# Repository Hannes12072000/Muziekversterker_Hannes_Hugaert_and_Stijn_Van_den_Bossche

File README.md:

# Muziekversterker_Hannes_Hugaert_and_Stijn_Van_den_bossche
 
onderwerp:  Touch muziekversterker
naam:   Hannes Hugaert & Stijn Van den bossche

Korte beschrijving:
Wij gaan een muziekversterker maken die voorzien is van 2 channels en een microfoon. Op deze versterker kunnen we de tonen regelen (treble, medium en bass) maar we kunnen ook het volume regelen. Onze sliders zijn geen gewone mechanische sliders, we voorzien touchpads als sliders. Om feedback over het volume en de tonen te geven, voorzien we ledjes naast de touchpads om het huidige niveau weer te geven.

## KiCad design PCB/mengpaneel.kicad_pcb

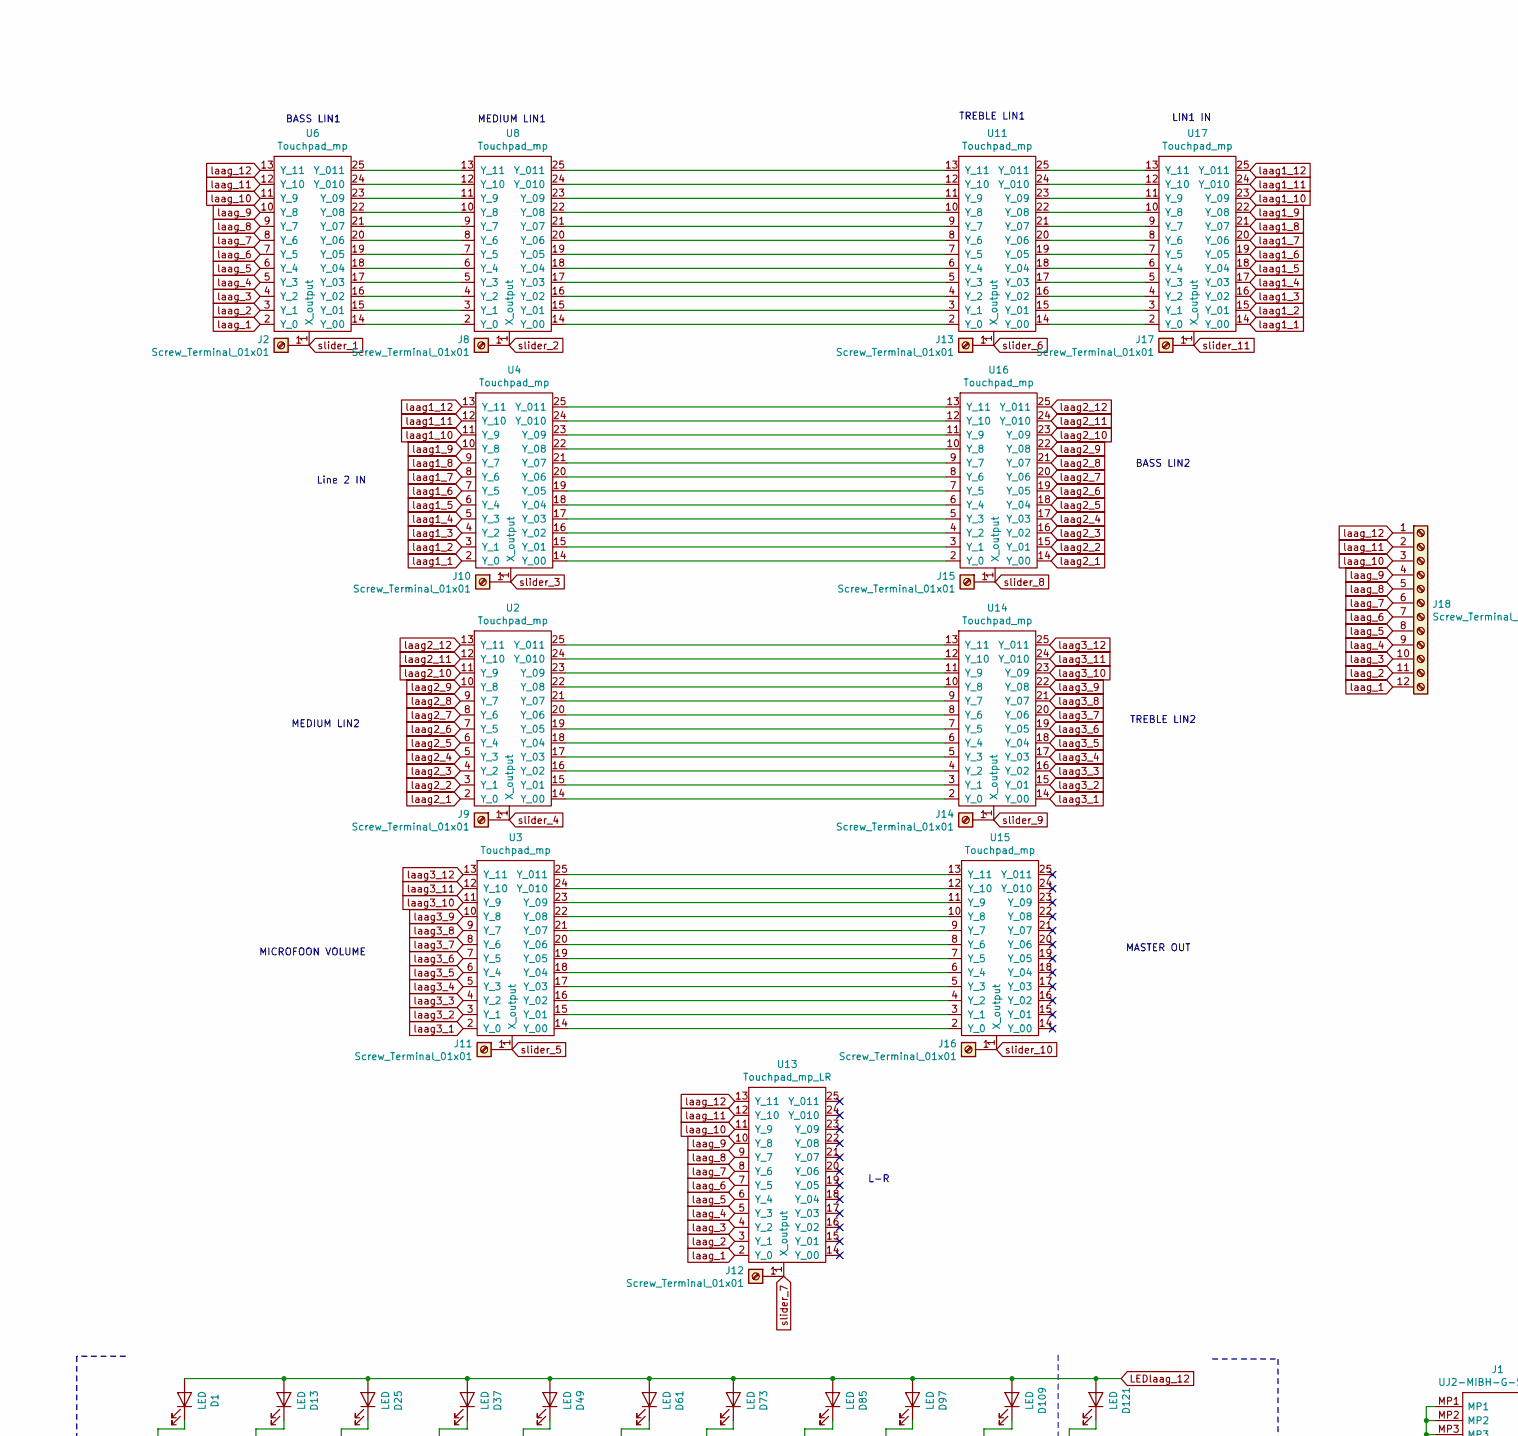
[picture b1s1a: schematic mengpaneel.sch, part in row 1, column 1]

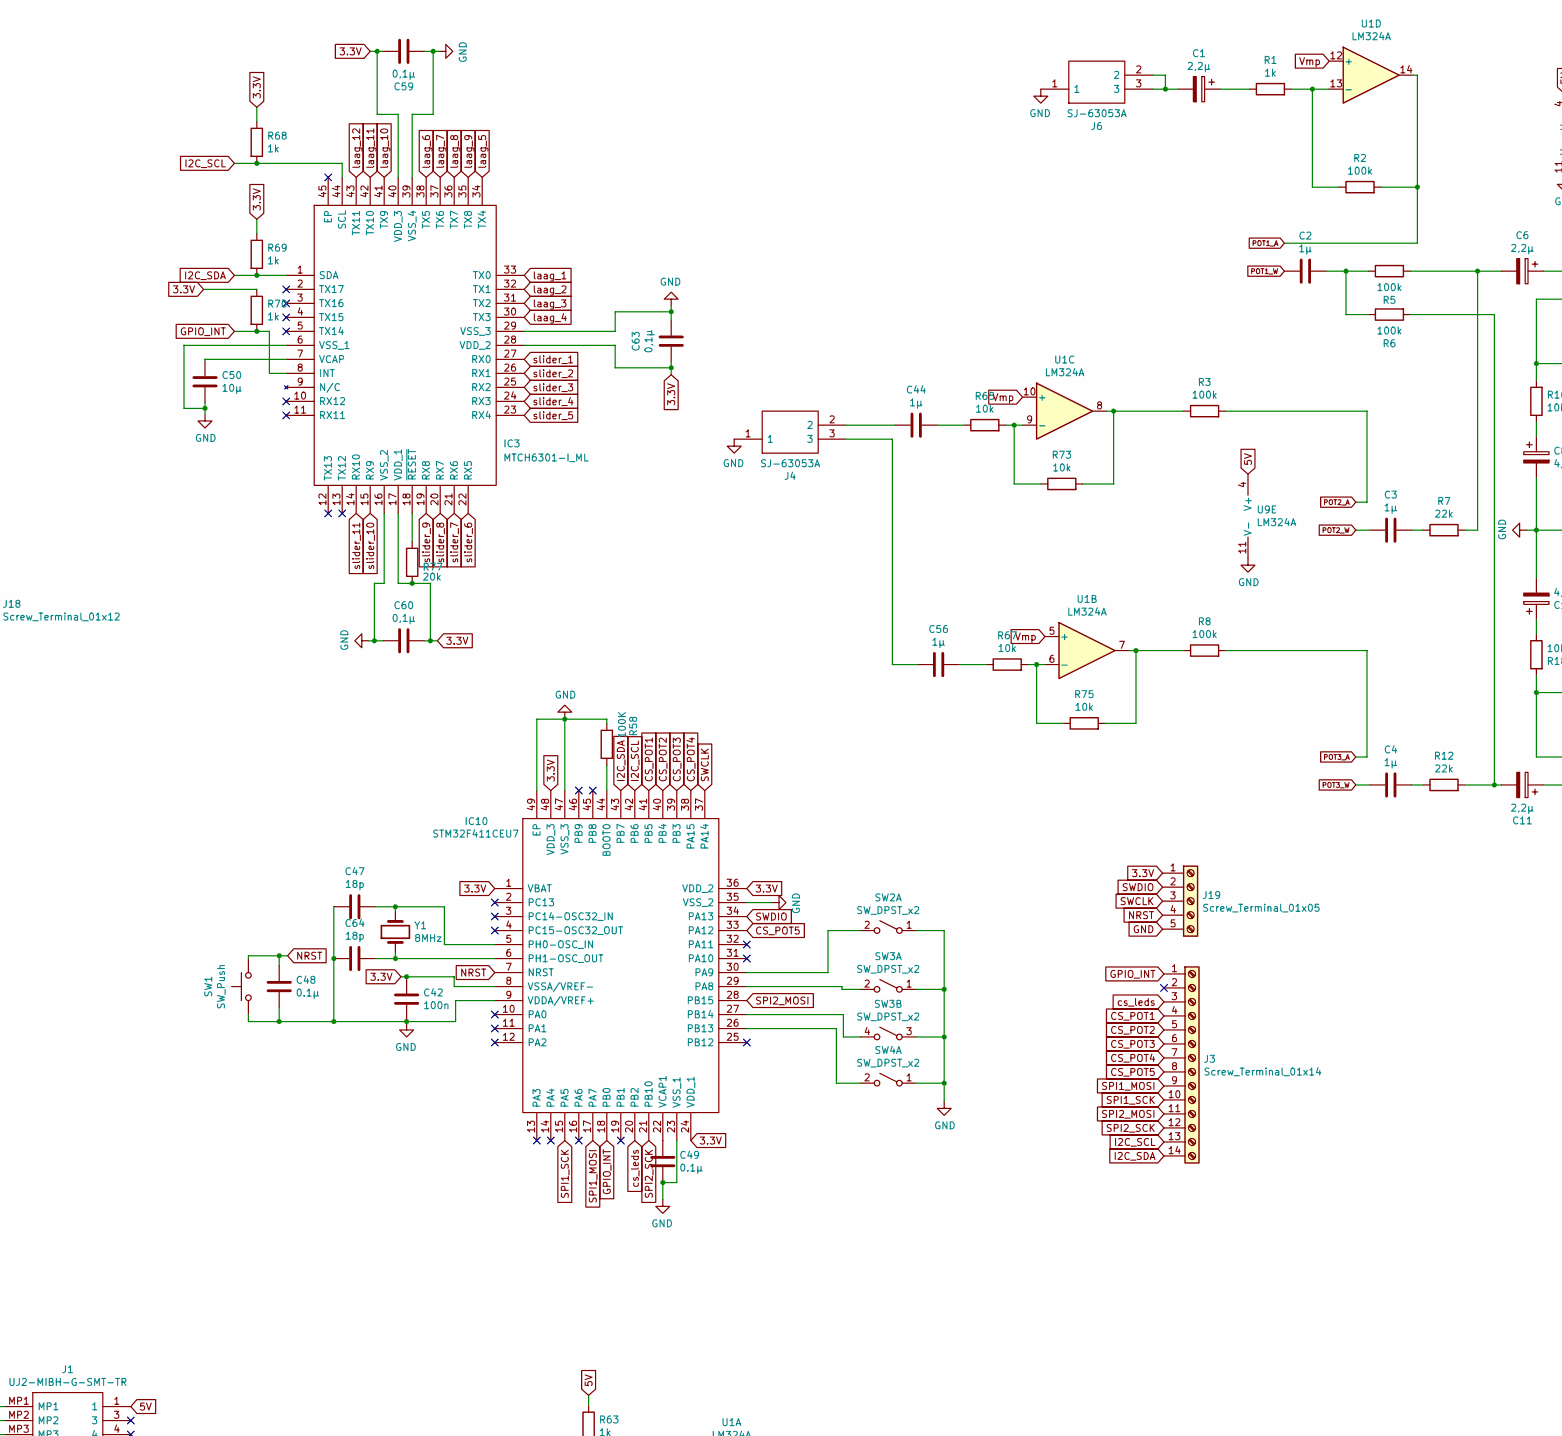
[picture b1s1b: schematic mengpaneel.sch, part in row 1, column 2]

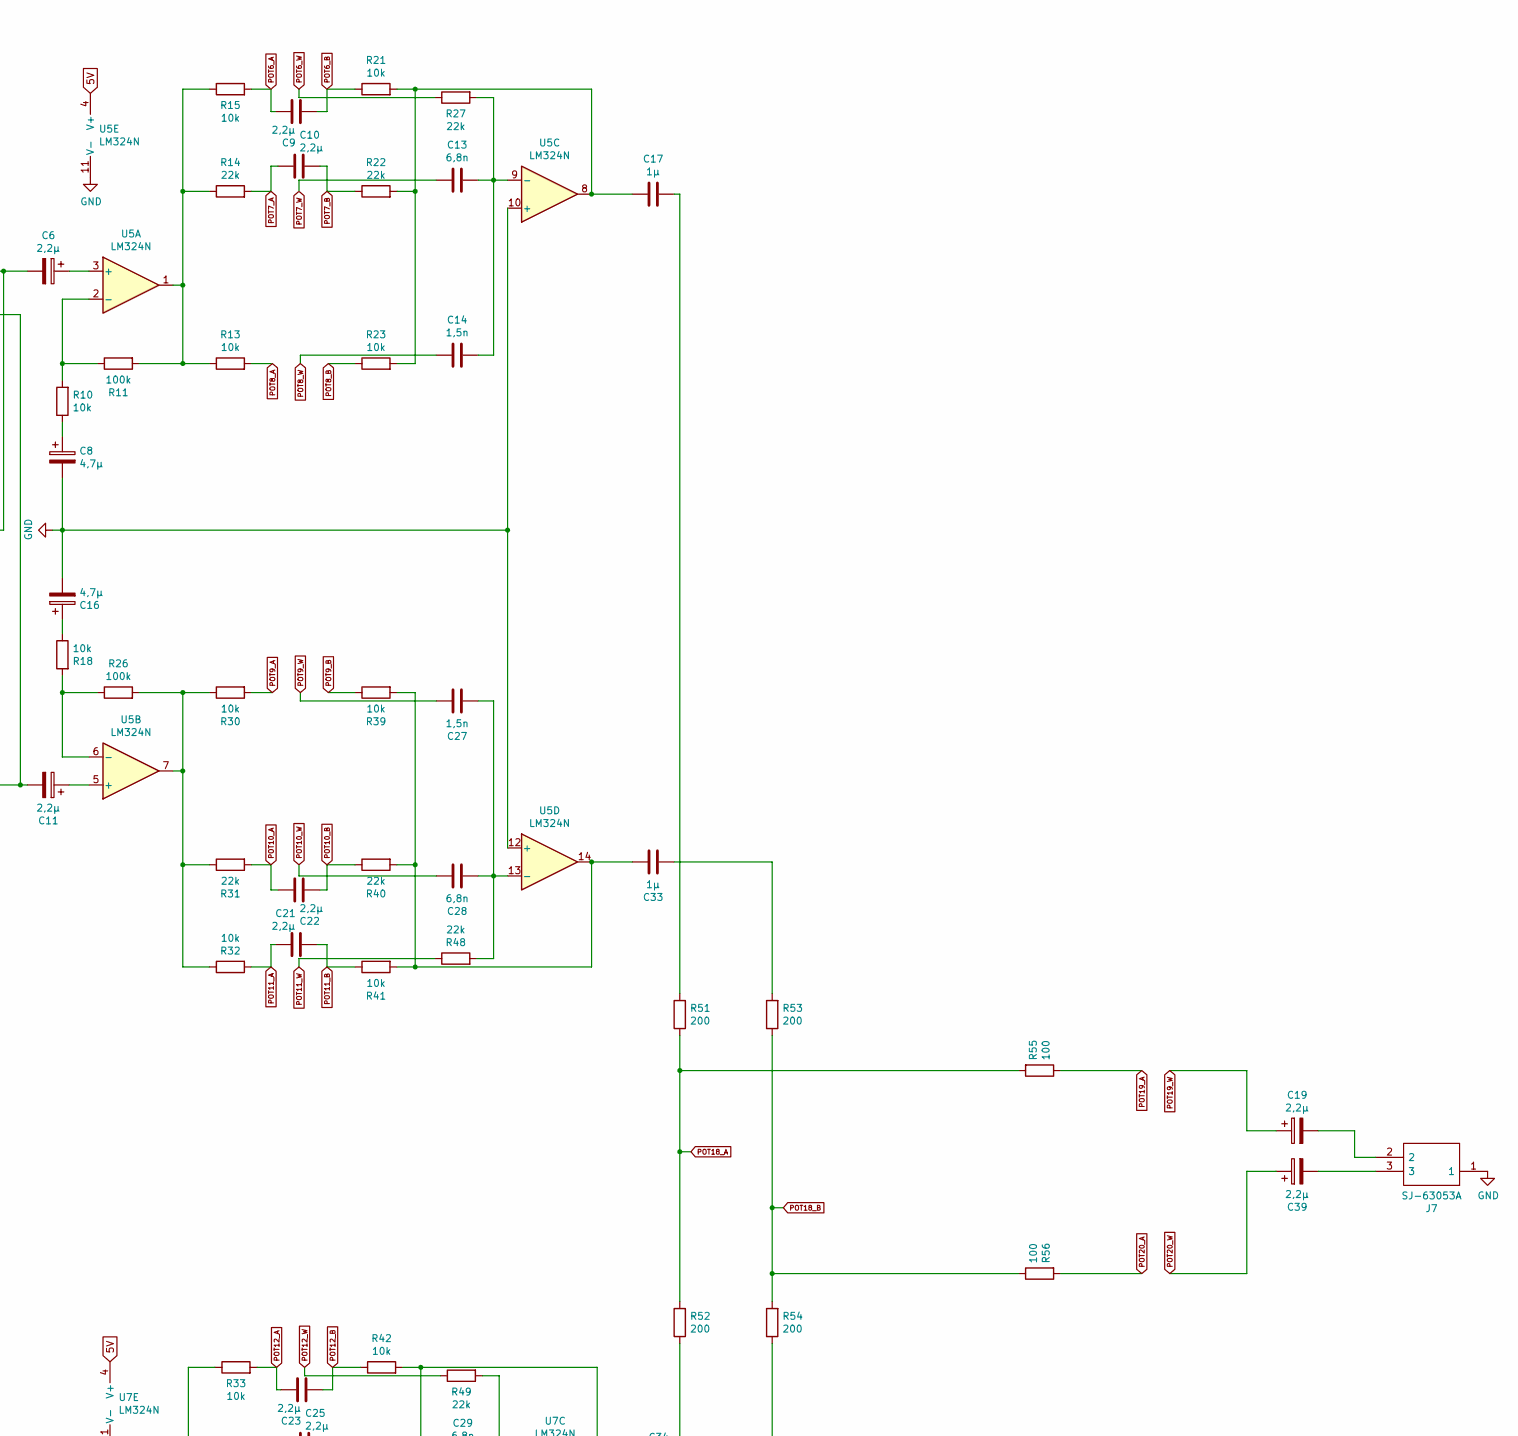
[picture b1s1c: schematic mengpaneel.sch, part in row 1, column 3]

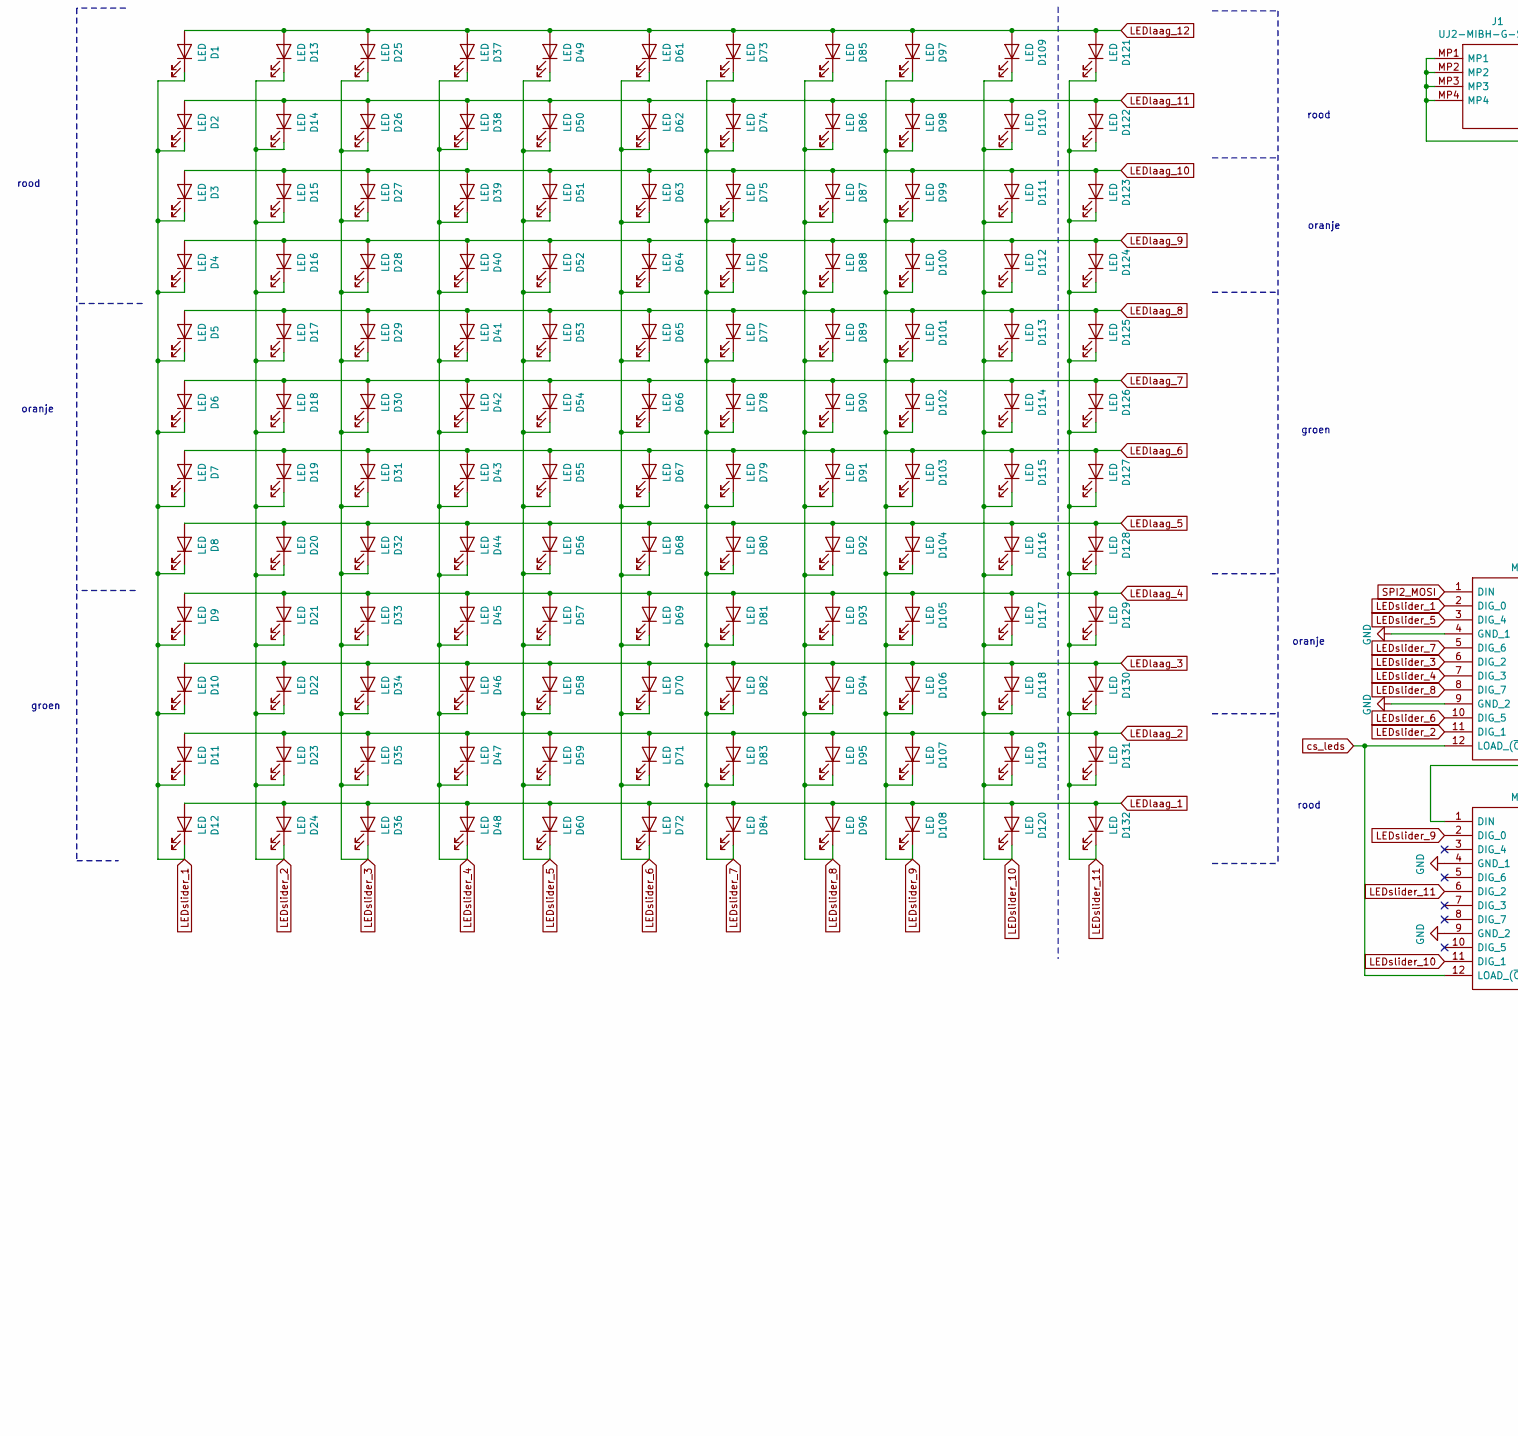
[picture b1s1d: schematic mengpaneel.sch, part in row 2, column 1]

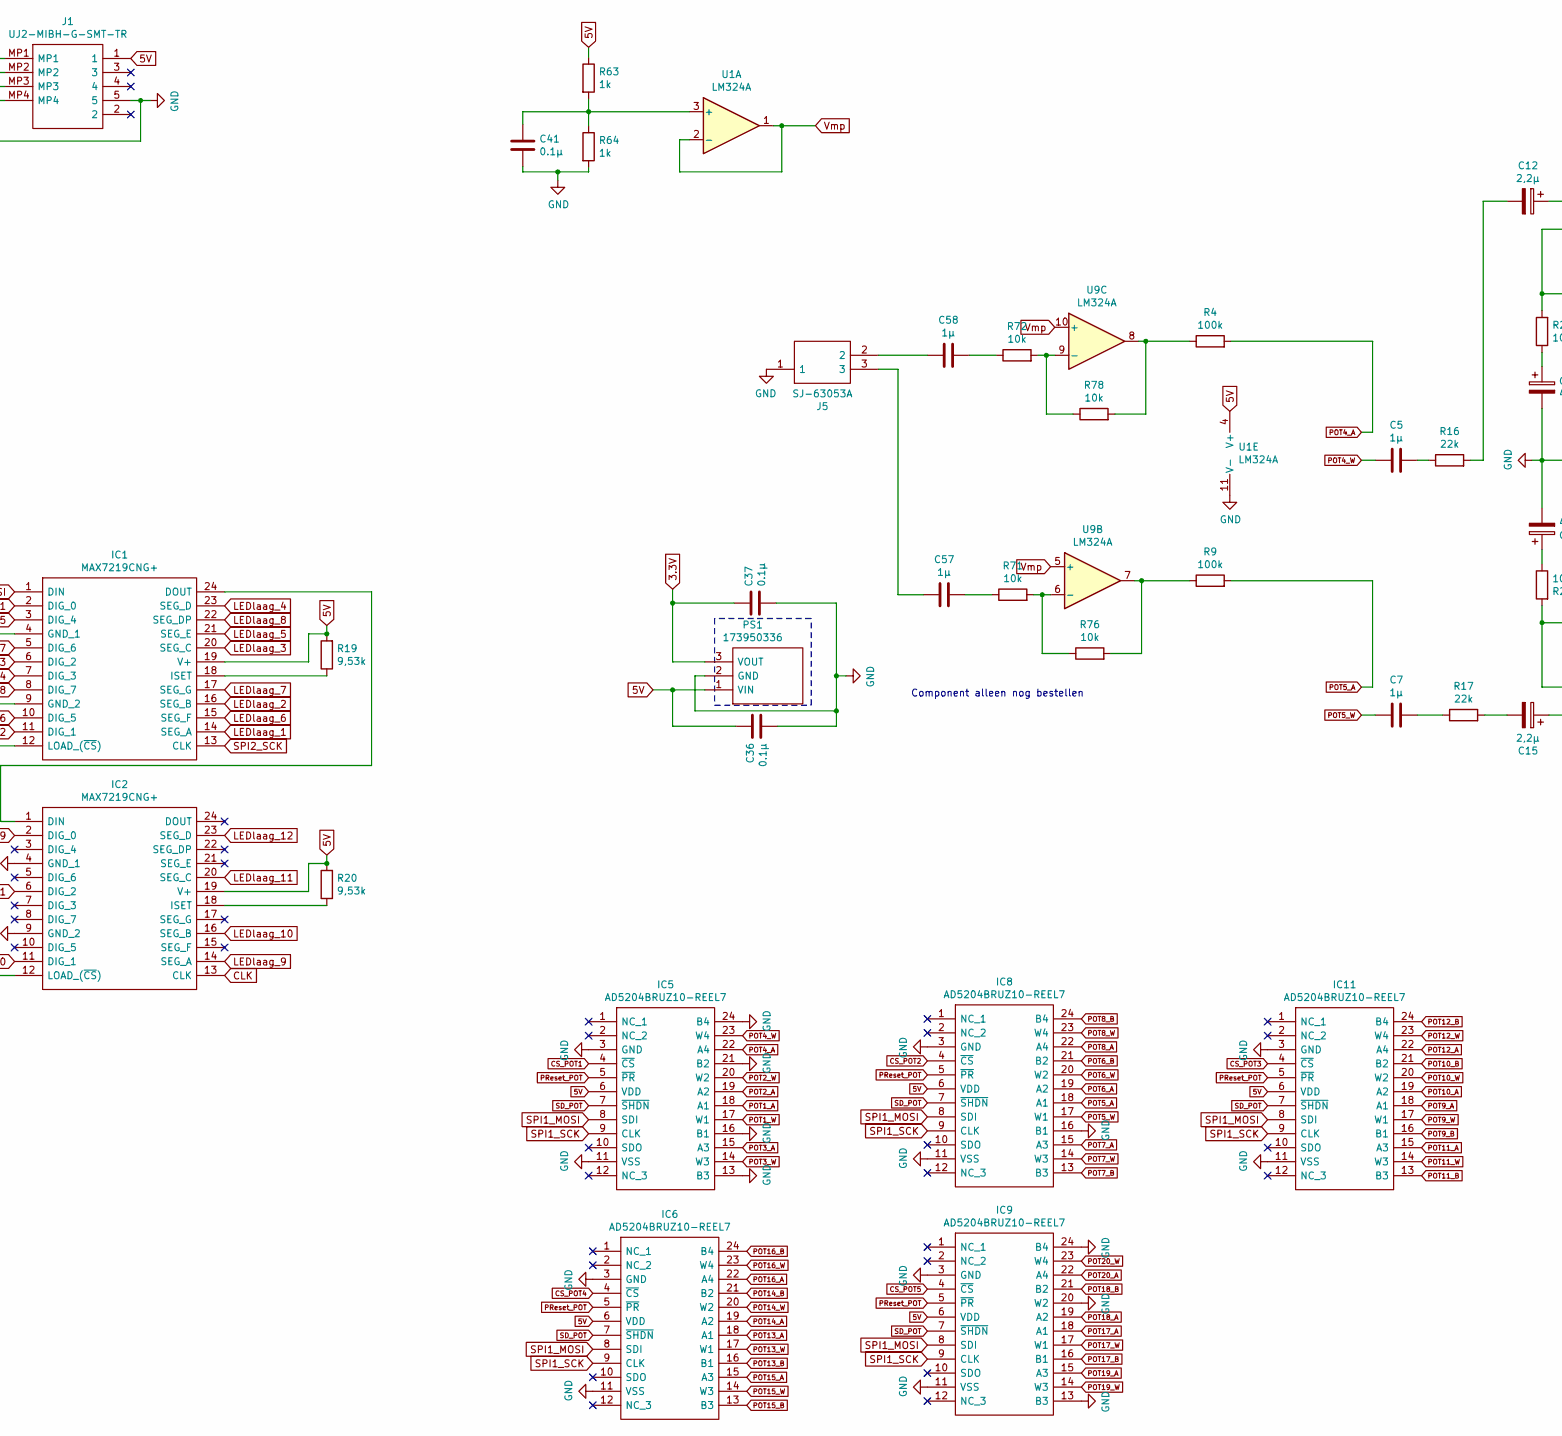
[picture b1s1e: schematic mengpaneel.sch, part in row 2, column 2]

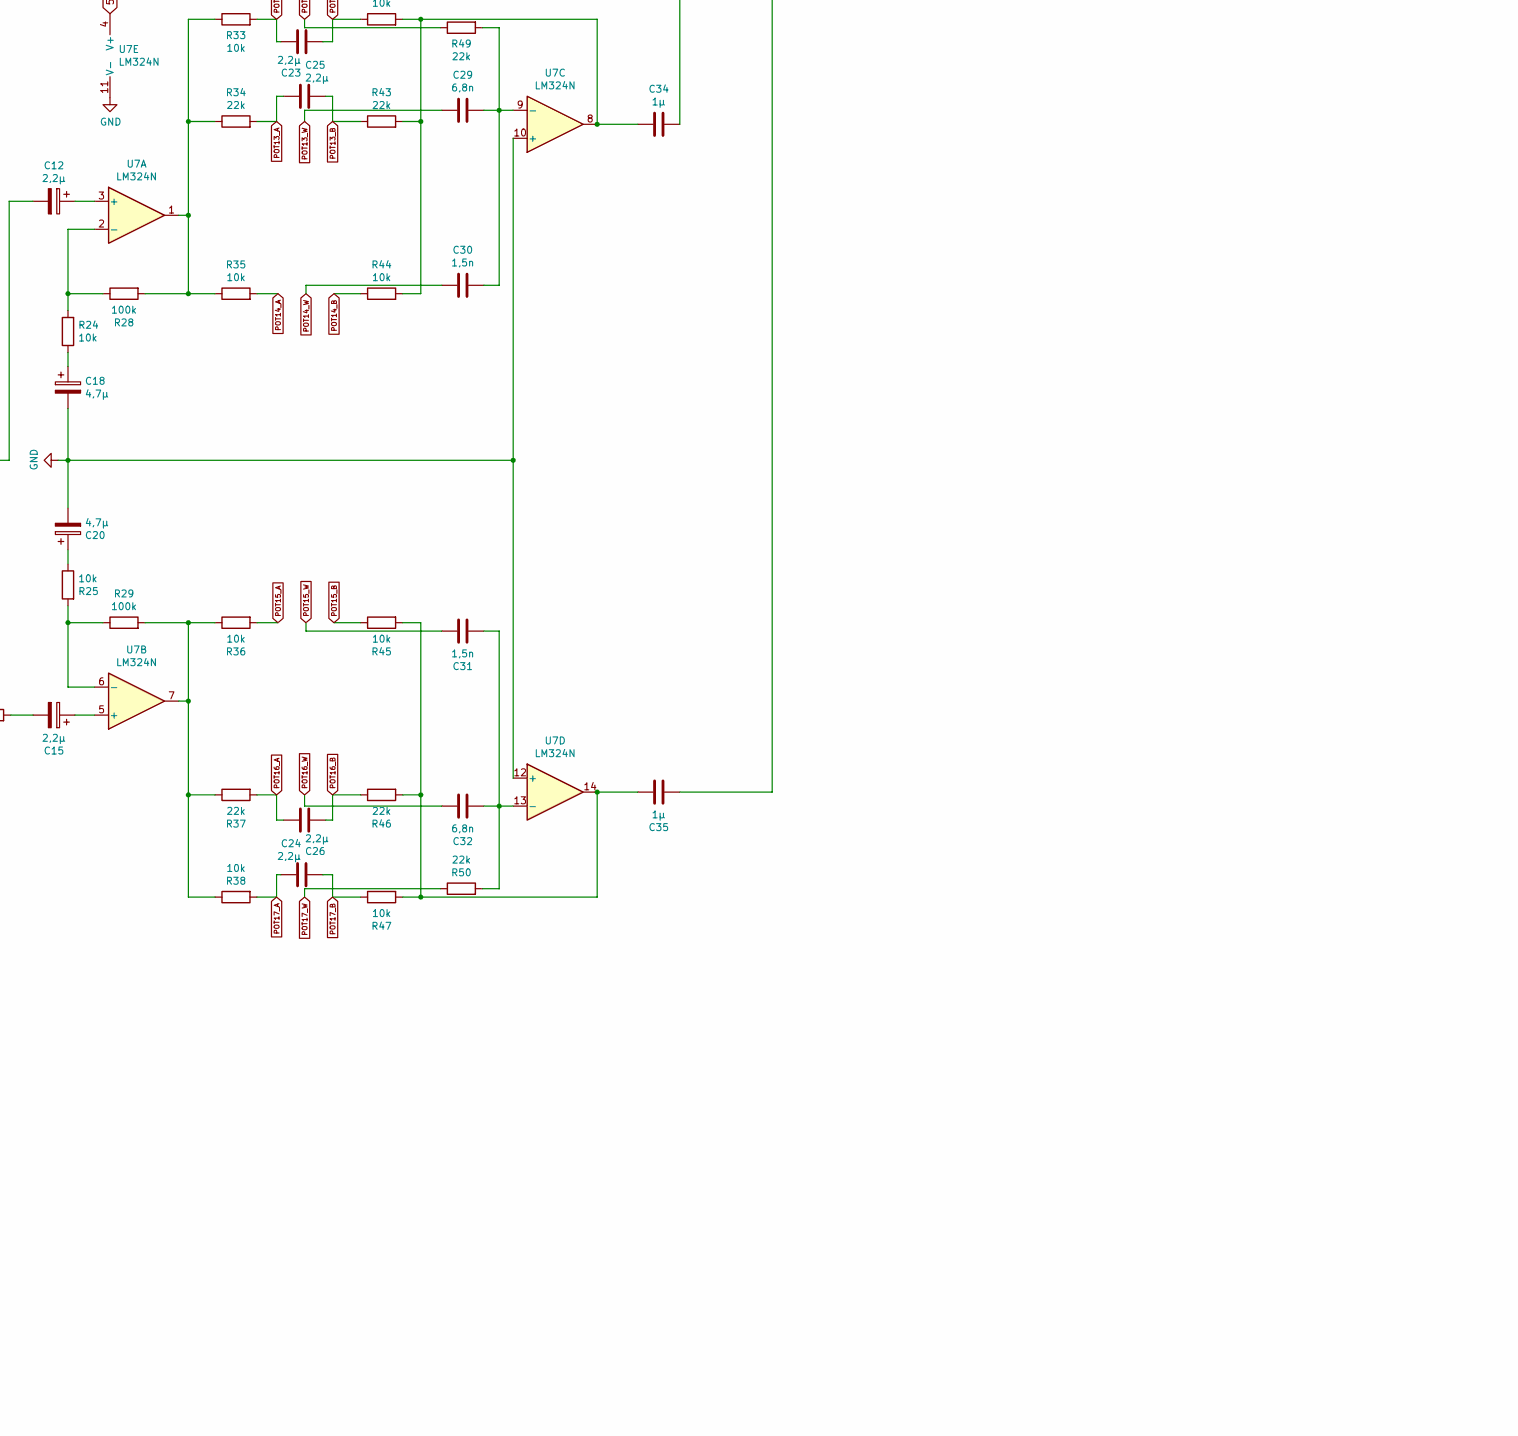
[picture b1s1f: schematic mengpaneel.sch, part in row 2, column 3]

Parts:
C1, C6, C11, C12, C15, C19, C39: 2,2µ; CAPAE1050X1050N
C2, C3, C4, C5, C7, C17, C33, C34, C35, C44, C56, C57, C58: 1µ; CAPC2012X100N
C8, C16, C18, C20: 4,7µ; CAPAE660X610N
C9, C10, C21, C22, C23, C24, C25, C26: 2,2µ; CAPC2012X135N
C13, C28, C29, C32: 6,8n; CAPC2012X100N
C14, C27, C30, C31: 1,5n; CAPC1005X55N
C36, C37, C41, C48, C49: 0.1µ; CAPC1608X90N
C42: 100n; CAPC3216X88N
C47, C64: 18p; CAPC1005X55N
C50: 10µ; CAPC2114X145N
C59, C60, C63: 0,1µ; CAPC1608X90N
D1, D2, D3, D4, D5, D6, D7, D8, D9, D10, D11, D12, D13, D14, D15, D16, D17, D18, D19, D20, D21, D22, D23, D24, D25, D26, D27, D28, D29, D30, D31, D32, D33, D34, D35, D36, D37, D38, D39, D40, D41, D42, D43, D44, D45, D46, D47, D48, D49, D50, D51, D52, D53, D54, D55, D56, D57, D58, D59, D60, D61, D62, D63, D64, D65, D66, D67, D68, D69, D70, D71, D72, D73, D74, D75, D76, D77, D78, D79, D80, D81, D82, D83, D84, D85, D86, D87, D88, D89, D90, D91, D92, D93, D94, D95, D96, D97, D98, D99, D100, D101, D102, D103, D104, D105, D106, D107, D108, D109, D110, D111, D112, D113, D114, D115, D116, D117, D118, D119, D120, D121, D122, D123, D124, D125, D126, D127, D128, D129, D130, D131, D132: LED; LEDM2214X135N
IC1, IC2: MAX7219CNG+; DIP794W56P254L3054H457Q24N; Mouser Part Number 700-MAX7219CNG
IC3: MTCH6301-I_ML; QFN65P800X800X100-45N-D; Mouser Part Number 579-MTCH6301-I/ML
IC5, IC6, IC8, IC9, IC11: AD5204BRUZ10-REEL7; SOP65P640X120-24N; Mouser Part Number 584-AD5204BRUZ10-R7
IC10: STM32F411CEU7; QFN50P700X700X65-49N-D; Mouser Part Number 511-STM32F411CEU7
J1: UJ2-MIBH-G-SMT-TR; UJ2MIBHGSMTTR; Mouser Part Number 490-UJ2-MIBH-G-SMTTR
J2, J8, J9, J10, J11, J12, J13, J14, J15, J16, J17: Screw_Terminal_01x01; PinHeader_1x01_P1.00mm_Vertical
J3: Screw_Terminal_01x14; PinHeader_1x14_P1.00mm_Vertical
J4, J5, J6, J7: SJ-63053A; SJ63053A; Mouser Part Number 490-SJ-63053A
J18: Screw_Terminal_01x12; PinHeader_1x12_P1.00mm_Vertical
J19: Screw_Terminal_01x05; PinHeader_1x05_P1.00mm_Vertical
PS1: 173950336; Mouser Part Number 710-173950336
R1, R63, R64, R68, R69, R70: 1k; RESC1005X40N
R2, R3, R4, R5, R6, R8, R9, R11, R26, R28, R29: 100k; RESC1608X55N
R7, R12, R14, R16, R17, R22, R27, R31, R34, R37, R40, R43, R46, R48, R49, R50: 22k; RESC3216X65N
R10, R13, R15, R18, R21, R23, R24, R25, R30, R32, R33, R35, R36, R38, R39, R41, R42, R44, R45, R47, R65, R67, R71, R72, R73, R75, R76, R78: 10k; RESC5025X70N
R19, R20: 9,53k; RESC2012X60N
R51, R52, R53, R54: 200; RESC5025X70N
R55, R56: 100; RESC5025X70N
R58: 100K; RESC1608X55N
R77: 20k; RESC1005X40N
SW1: SW_Push; PTS526SK15SMTR2LFS
SW2, SW3, SW4: SW_DPST_x2; PinHeader_1x04_P1.00mm_Vertical
U1, U9: LM324A; DIP794W56P254L1905H533Q14N
U2, U3, U4, U6, U8, U11, U14, U15, U16, U17: Touchpad_mp; touchpad_footprint_normaal
U5, U7: LM324N; DIP794W56P254L1905H533Q14N
U13: Touchpad_mp_LR; touchpad_footprint_LR
Y1: 8MHz; ECS80184XCKM

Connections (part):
3.3V: C37.1, C42.1, C59.1, C60.1, C63.1, IC3.17 (VDD_1), IC3.28 (VDD_2), IC3.40 (VDD_3), IC10.1 (VBAT), IC10.8 (VSSA/VREF-), IC10.24 (VDD_1), IC10.36 (VDD_2), IC10.48 (VDD_3), J19.1, PS1.3 (VOUT), R68.1, R69.1, R70.1, R77.2
5V: C36.1, IC1.19 (V+), IC2.19 (V+), IC5.6 (VDD), IC6.6 (VDD), IC8.6 (VDD), IC9.6 (VDD), IC11.6 (VDD), J1.1, PS1.1 (VIN), R19.2, R20.2, R63.1, U1.4 (V+), U5.4 (V+), U7.4 (V+), U9.4 (V+)
CLK: IC2.13 (CLK)
CS_POT1: IC5.4 (~CS), IC10.41 (PB5), J3.4
CS_POT2: IC8.4 (~CS), IC10.40 (PB4), J3.5
CS_POT3: IC10.39 (PB3), IC11.4 (~CS), J3.6
CS_POT4: IC6.4 (~CS), IC10.38 (PA15), J3.7
CS_POT5: IC9.4 (~CS), IC10.33 (PA12), J3.8
GND: C8.2, C16.2, C18.2, C20.2, C36.2, C37.2, C41.2, C42.2, C47.2, C48.2, C49.2, C50.2, C59.2, C60.2, C63.2, C64.1, IC1.4 (GND_1), IC1.9 (GND_2), IC2.4 (GND_1), IC2.9 (GND_2), IC3.6 (VSS_1), IC3.16 (VSS_2), IC3.29 (VSS_3), IC3.39 (VSS_4), IC5.3 (GND), IC5.11 (VSS), IC5.13 (B3), IC5.16 (B1), IC5.21 (B2), IC5.24 (B4), IC6.3 (GND), IC6.11 (VSS), IC8.3 (GND), IC8.11 (VSS), IC8.16 (B1), IC9.3 (GND), IC9.11 (VSS), IC9.13 (B3), IC9.20 (W2), IC9.24 (B4), IC10.9 (VDDA/VREF+), IC10.23 (VSS_1), IC10.35 (VSS_2), IC10.47 (VSS_3), IC10.49 (EP), IC11.3 (GND), IC11.11 (VSS), J1.5, J1.MP1, J1.MP2, J1.MP3, J1.MP4, J4.1, J5.1, J6.1, J7.1, J19.5, PS1.2 (GND), R58.2, R64.2, SW1.1, SW2.1 (A), SW3.1 (A), SW3.3 (A), SW4.1 (A), U1.11 (V-), U5.10 (+), U5.11 (V-), U5.12 (+), U7.10 (+), U7.11 (V-), U7.12 (+), U9.11 (V-)
GPIO_INT: IC3.8 (INT), IC10.18 (PB0), J3.1, R70.2
I2C_SCL: IC3.44 (SCL), IC10.42 (PB6), J3.13, R68.2
I2C_SDA: IC3.1 (SDA), IC10.43 (PB7), J3.14, R69.2
LEDlaag_1: D12.2 (A), D24.2 (A), D36.2 (A), D48.2 (A), D60.2 (A), D72.2 (A), D84.2 (A), D96.2 (A), D108.2 (A), D120.2 (A), D132.2 (A), IC1.14 (SEG_A)
LEDlaag_2: D11.2 (A), D23.2 (A), D35.2 (A), D47.2 (A), D59.2 (A), D71.2 (A), D83.2 (A), D95.2 (A), D107.2 (A), D119.2 (A), D131.2 (A), IC1.16 (SEG_B)
LEDlaag_3: D10.2 (A), D22.2 (A), D34.2 (A), D46.2 (A), D58.2 (A), D70.2 (A), D82.2 (A), D94.2 (A), D106.2 (A), D118.2 (A), D130.2 (A), IC1.20 (SEG_C)
LEDlaag_4: D9.2 (A), D21.2 (A), D33.2 (A), D45.2 (A), D57.2 (A), D69.2 (A), D81.2 (A), D93.2 (A), D105.2 (A), D117.2 (A), D129.2 (A), IC1.23 (SEG_D)
LEDlaag_5: D8.2 (A), D20.2 (A), D32.2 (A), D44.2 (A), D56.2 (A), D68.2 (A), D80.2 (A), D92.2 (A), D104.2 (A), D116.2 (A), D128.2 (A), IC1.21 (SEG_E)
LEDlaag_6: D7.2 (A), D19.2 (A), D31.2 (A), D43.2 (A), D55.2 (A), D67.2 (A), D79.2 (A), D91.2 (A), D103.2 (A), D115.2 (A), D127.2 (A), IC1.15 (SEG_F)
LEDlaag_7: D6.2 (A), D18.2 (A), D30.2 (A), D42.2 (A), D54.2 (A), D66.2 (A), D78.2 (A), D90.2 (A), D102.2 (A), D114.2 (A), D126.2 (A), IC1.17 (SEG_G)
LEDlaag_8: D5.2 (A), D17.2 (A), D29.2 (A), D41.2 (A), D53.2 (A), D65.2 (A), D77.2 (A), D89.2 (A), D101.2 (A), D113.2 (A), D125.2 (A), IC1.22 (SEG_DP)
LEDlaag_9: D4.2 (A), D16.2 (A), D28.2 (A), D40.2 (A), D52.2 (A), D64.2 (A), D76.2 (A), D88.2 (A), D100.2 (A), D112.2 (A), D124.2 (A), IC2.14 (SEG_A)
LEDlaag_10: D3.2 (A), D15.2 (A), D27.2 (A), D39.2 (A), D51.2 (A), D63.2 (A), D75.2 (A), D87.2 (A), D99.2 (A), D111.2 (A), D123.2 (A), IC2.16 (SEG_B)
LEDlaag_11: D2.2 (A), D14.2 (A), D26.2 (A), D38.2 (A), D50.2 (A), D62.2 (A), D74.2 (A), D86.2 (A), D98.2 (A), D110.2 (A), D122.2 (A), IC2.20 (SEG_C)
LEDlaag_12: D1.2 (A), D13.2 (A), D25.2 (A), D37.2 (A), D49.2 (A), D61.2 (A), D73.2 (A), D85.2 (A), D97.2 (A), D109.2 (A), D121.2 (A), IC2.23 (SEG_D)
LEDslider_1: D1.1 (K), D2.1 (K), D3.1 (K), D4.1 (K), D5.1 (K), D6.1 (K), D7.1 (K), D8.1 (K), D9.1 (K), D10.1 (K), D11.1 (K), D12.1 (K), IC1.2 (DIG_0)
LEDslider_2: D13.1 (K), D14.1 (K), D15.1 (K), D16.1 (K), D17.1 (K), D18.1 (K), D19.1 (K), D20.1 (K), D21.1 (K), D22.1 (K), D23.1 (K), D24.1 (K), IC1.11 (DIG_1)
LEDslider_3: D25.1 (K), D26.1 (K), D27.1 (K), D28.1 (K), D29.1 (K), D30.1 (K), D31.1 (K), D32.1 (K), D33.1 (K), D34.1 (K), D35.1 (K), D36.1 (K), IC1.6 (DIG_2)
LEDslider_4: D37.1 (K), D38.1 (K), D39.1 (K), D40.1 (K), D41.1 (K), D42.1 (K), D43.1 (K), D44.1 (K), D45.1 (K), D46.1 (K), D47.1 (K), D48.1 (K), IC1.7 (DIG_3)
LEDslider_5: D49.1 (K), D50.1 (K), D51.1 (K), D52.1 (K), D53.1 (K), D54.1 (K), D55.1 (K), D56.1 (K), D57.1 (K), D58.1 (K), D59.1 (K), D60.1 (K), IC1.3 (DIG_4)
LEDslider_6: D61.1 (K), D62.1 (K), D63.1 (K), D64.1 (K), D65.1 (K), D66.1 (K), D67.1 (K), D68.1 (K), D69.1 (K), D70.1 (K), D71.1 (K), D72.1 (K), IC1.10 (DIG_5)
LEDslider_7: D73.1 (K), D74.1 (K), D75.1 (K), D76.1 (K), D77.1 (K), D78.1 (K), D79.1 (K), D80.1 (K), D81.1 (K), D82.1 (K), D83.1 (K), D84.1 (K), IC1.5 (DIG_6)
LEDslider_8: D85.1 (K), D86.1 (K), D87.1 (K), D88.1 (K), D89.1 (K), D90.1 (K), D91.1 (K), D92.1 (K), D93.1 (K), D94.1 (K), D95.1 (K), D96.1 (K), IC1.8 (DIG_7)
LEDslider_9: D97.1 (K), D98.1 (K), D99.1 (K), D100.1 (K), D101.1 (K), D102.1 (K), D103.1 (K), D104.1 (K), D105.1 (K), D106.1 (K), D107.1 (K), D108.1 (K), IC2.2 (DIG_0)
LEDslider_10: D109.1 (K), D110.1 (K), D111.1 (K), D112.1 (K), D113.1 (K), D114.1 (K), D115.1 (K), D116.1 (K), D117.1 (K), D118.1 (K), D119.1 (K), D120.1 (K), IC2.11 (DIG_1)
LEDslider_11: D121.1 (K), D122.1 (K), D123.1 (K), D124.1 (K), D125.1 (K), D126.1 (K), D127.1 (K), D128.1 (K), D129.1 (K), D130.1 (K), D131.1 (K), D132.1 (K), IC2.6 (DIG_2)
NRST: C48.1, IC10.7 (NRST), J19.4, SW1.2
unnamed: C1.1, R1.1
unnamed: C1.2, J6.2, J6.3
unnamed: C2.2, R5.1, R6.1
unnamed: C3.2, R7.1
unnamed: C4.2, R12.1
unnamed: C5.2, R16.1
unnamed: C6.1, U5.3 (+)
unnamed: C6.2, R5.2, R7.2
unnamed: C7.2, R17.1
unnamed: C8.1, R10.1
unnamed: C11.1, U5.5 (+)
unnamed: C11.2, R6.2, R12.2
unnamed: C12.1, U7.3 (+)
unnamed: C12.2, R16.2
unnamed: C13.2, C14.2, R27.2, U5.9 (-)
unnamed: C15.1, U7.5 (+)
unnamed: C15.2, R17.2
unnamed: C16.1, R18.1
unnamed: C17.1, R21.2, R22.2, R23.2, U5.8
unnamed: C17.2, R51.2
unnamed: C18.1, R24.1
unnamed: C19.2, J7.2
unnamed: C20.1, R25.1
unnamed: C27.2, C28.2, R48.2, U5.13 (-)
unnamed: C29.2, C30.2, R49.2, U7.9 (-)
unnamed: C31.2, C32.2, R50.2, U7.13 (-)
unnamed: C33.1, R39.2, R40.2, R41.2, U5.14
unnamed: C33.2, R53.2
unnamed: C34.1, R42.2, R43.2, R44.2, U7.8
unnamed: C34.2, R52.1
unnamed: C35.1, R45.2, R46.2, R47.2, U7.14
unnamed: C35.2, R54.1
unnamed: C39.2, J7.3
unnamed: C41.1, R63.2, R64.1, U1.3 (+)
unnamed: C44.1, J4.2
unnamed: C44.2, R65.1
unnamed: C47.1, IC10.5 (PH0-OSC_IN), Y1.2
unnamed: C49.1, IC10.22 (VCAP1)
unnamed: C50.1, IC3.7 (VCAP)
unnamed: C56.1, J4.3
unnamed: C56.2, R67.1
unnamed: C57.1, J5.3
unnamed: C57.2, R71.1
unnamed: C58.1, J5.2
unnamed: C58.2, R72.1
unnamed: C64.2, IC10.6 (PH1-OSC_OUT), Y1.1
unnamed: IC1.18 (ISET), R19.1
unnamed: IC1.24 (DOUT), IC2.1 (DIN)
unnamed: IC2.18 (ISET), R20.1
unnamed: IC3.18 (~RESET), R77.1
unnamed: IC10.26 (PB13), SW4.2 (B)
unnamed: IC10.27 (PB14), SW3.4 (B)
unnamed: IC10.29 (PA8), SW3.2 (B)
unnamed: IC10.30 (PA9), SW2.2 (B)
unnamed: IC10.44 (BOOT0), R58.1
unnamed: R1.2, R2.1, U1.13 (-)
unnamed: R3.1, R73.2, U1.8
unnamed: R4.1, R78.2, U9.8
unnamed: R10.2, R11.1, U5.2 (-)
unnamed: R11.2, R13.1, R14.1, R15.1, U5.1
unnamed: R18.2, R26.1, U5.6 (-)
unnamed: R24.2, R28.1, U7.2 (-)
unnamed: R25.2, R29.1, U7.6 (-)
unnamed: R26.2, R30.1, R31.1, R32.1, U5.7
unnamed: R28.2, R33.1, R34.1, R35.1, U7.1
unnamed: R29.2, R36.1, R37.1, R38.1, U7.7
unnamed: R65.2, R73.1, U1.9 (-)
unnamed: R67.2, R75.1, U1.6 (-)
unnamed: R71.2, R76.1, U9.6 (-)
unnamed: R72.2, R78.1, U9.9 (-)
unnamed: R8.1, R75.2, U1.7
unnamed: R9.1, R76.2, U9.7
unnamed: U6.14 (Y_00), U8.2 (Y_0)
unnamed: U6.15 (Y_01), U8.3 (Y_1)
unnamed: U6.16 (Y_02), U8.4 (Y_2)
unnamed: U6.17 (Y_03), U8.5 (Y_3)
unnamed: U6.18 (Y_04), U8.6 (Y_4)
unnamed: U6.19 (Y_05), U8.7 (Y_5)
unnamed: U6.20 (Y_06), U8.8 (Y_6)
unnamed: U6.21 (Y_07), U8.9 (Y_7)
unnamed: U6.22 (Y_08), U8.10 (Y_8)
unnamed: U6.23 (Y_09), U8.11 (Y_9)
unnamed: U6.24 (Y_010), U8.12 (Y_10)
unnamed: U6.25 (Y_011), U8.13 (Y_11)
unnamed: U8.14 (Y_00), U11.2 (Y_0)
unnamed: U8.15 (Y_01), U11.3 (Y_1)
unnamed: U8.16 (Y_02), U11.4 (Y_2)
unnamed: U8.17 (Y_03), U11.5 (Y_3)
unnamed: U8.18 (Y_04), U11.6 (Y_4)
unnamed: U8.19 (Y_05), U11.7 (Y_5)
unnamed: U8.20 (Y_06), U11.8 (Y_6)
unnamed: U8.21 (Y_07), U11.9 (Y_7)
unnamed: U8.22 (Y_08), U11.10 (Y_8)
unnamed: U8.23 (Y_09), U11.11 (Y_9)
unnamed: U8.24 (Y_010), U11.12 (Y_10)
unnamed: U8.25 (Y_011), U11.13 (Y_11)
unnamed: U11.14 (Y_00), U17.2 (Y_0)
unnamed: U11.15 (Y_01), U17.3 (Y_1)
unnamed: U11.16 (Y_02), U17.4 (Y_2)
unnamed: U11.17 (Y_03), U17.5 (Y_3)
unnamed: U11.18 (Y_04), U17.6 (Y_4)
unnamed: U11.19 (Y_05), U17.7 (Y_5)
unnamed: U11.20 (Y_06), U17.8 (Y_6)
unnamed: U11.21 (Y_07), U17.9 (Y_7)
unnamed: U11.22 (Y_08), U17.10 (Y_8)
unnamed: U11.23 (Y_09), U17.11 (Y_9)
unnamed: U11.24 (Y_010), U17.12 (Y_10)
unnamed: U11.25 (Y_011), U17.13 (Y_11)
unnamed: U2.14 (Y_00), U14.2 (Y_0)
unnamed: U2.15 (Y_01), U14.3 (Y_1)
unnamed: U2.16 (Y_02), U14.4 (Y_2)
unnamed: U2.17 (Y_03), U14.5 (Y_3)
unnamed: U2.18 (Y_04), U14.6 (Y_4)
unnamed: U2.19 (Y_05), U14.7 (Y_5)
unnamed: U2.20 (Y_06), U14.8 (Y_6)
unnamed: U2.21 (Y_07), U14.9 (Y_7)
unnamed: U2.22 (Y_08), U14.10 (Y_8)
unnamed: U2.23 (Y_09), U14.11 (Y_9)
unnamed: U2.24 (Y_010), U14.12 (Y_10)
unnamed: U2.25 (Y_011), U14.13 (Y_11)
unnamed: U3.14 (Y_00), U15.2 (Y_0)
unnamed: U3.15 (Y_01), U15.3 (Y_1)
unnamed: U3.16 (Y_02), U15.4 (Y_2)
unnamed: U3.17 (Y_03), U15.5 (Y_3)
unnamed: U3.18 (Y_04), U15.6 (Y_4)
unnamed: U3.19 (Y_05), U15.7 (Y_5)
unnamed: U3.20 (Y_06), U15.8 (Y_6)
unnamed: U3.21 (Y_07), U15.9 (Y_7)
unnamed: U3.22 (Y_08), U15.10 (Y_8)
unnamed: U3.23 (Y_09), U15.11 (Y_9)
unnamed: U3.24 (Y_010), U15.12 (Y_10)
unnamed: U3.25 (Y_011), U15.13 (Y_11)
unnamed: U4.14 (Y_00), U16.2 (Y_0)
unnamed: U4.15 (Y_01), U16.3 (Y_1)
unnamed: U4.16 (Y_02), U16.4 (Y_2)
unnamed: U4.17 (Y_03), U16.5 (Y_3)
unnamed: U4.18 (Y_04), U16.6 (Y_4)
unnamed: U4.19 (Y_05), U16.7 (Y_5)
unnamed: U4.20 (Y_06), U16.8 (Y_6)
unnamed: U4.21 (Y_07), U16.9 (Y_7)
unnamed: U4.22 (Y_08), U16.10 (Y_8)
unnamed: U4.23 (Y_09), U16.11 (Y_9)
unnamed: U4.24 (Y_010), U16.12 (Y_10)
unnamed: U4.25 (Y_011), U16.13 (Y_11)
POT1_A: IC5.18 (A1), R2.2, U1.14
POT1_W: C2.1, IC5.17 (W1)
POT2_A: IC5.19 (A2), R3.2
POT2_W: C3.1, IC5.20 (W2)
POT3_A: IC5.15 (A3), R8.2
POT3_W: C4.1, IC5.14 (W3)
POT4_A: IC5.22 (A4), R4.2
POT4_W: C5.1, IC5.23 (W4)
POT5_A: IC8.18 (A1), R9.2
POT5_W: C7.1, IC8.17 (W1)
POT6_A: C9.1, IC8.19 (A2), R15.2
POT6_B: C9.2, IC8.21 (B2), R21.1
POT6_W: IC8.20 (W2), R27.1
POT7_A: C10.1, IC8.15 (A3), R14.2
POT7_B: C10.2, IC8.13 (B3), R22.1
POT7_W: C13.1, IC8.14 (W3)
POT8_A: IC8.22 (A4), R13.2
POT8_B: IC8.24 (B4), R23.1
POT8_W: C14.1, IC8.23 (W4)
POT9_A: IC11.18 (A1), R30.2
POT9_B: IC11.16 (B1), R39.1
POT9_W: C27.1, IC11.17 (W1)
POT10_A: C22.1, IC11.19 (A2), R31.2
POT10_B: C22.2, IC11.21 (B2), R40.1
POT10_W: C28.1, IC11.20 (W2)
POT11_A: C21.1, IC11.15 (A3), R32.2
POT11_B: C21.2, IC11.13 (B3), R41.1
POT11_W: IC11.14 (W3), R48.1
POT12_A: C23.1, IC11.22 (A4), R33.2
POT12_B: C23.2, IC11.24 (B4), R42.1
POT12_W: IC11.23 (W4), R49.1
POT13_A: C25.1, IC6.18 (A1), R34.2
POT13_B: C25.2, IC6.16 (B1), R43.1
POT13_W: C29.1, IC6.17 (W1)
POT14_A: IC6.19 (A2), R35.2
POT14_B: IC6.21 (B2), R44.1
POT14_W: C30.1, IC6.20 (W2)
POT15_A: IC6.15 (A3), R36.2
POT15_B: IC6.13 (B3), R45.1
POT15_W: C31.1, IC6.14 (W3)
POT16_A: C26.1, IC6.22 (A4), R37.2
POT16_B: C26.2, IC6.24 (B4), R46.1
POT16_W: C32.1, IC6.23 (W4)
POT17_A: C24.1, IC9.18 (A1), R38.2
POT17_B: C24.2, IC9.16 (B1), R47.1
POT17_W: IC9.17 (W1), R50.1
POT18_A: IC9.19 (A2), R51.1, R52.2, R55.2
POT18_B: IC9.21 (B2), R53.1, R54.2, R56.1
POT19_A: IC9.15 (A3), R55.1
POT19_W: C19.1, IC9.14 (W3)
POT20_A: IC9.22 (A4), R56.2
POT20_W: C39.1, IC9.23 (W4)
PReset_POT: IC5.5 (~PR), IC6.5 (~PR), IC8.5 (~PR), IC9.5 (~PR), IC11.5 (~PR)
SD_POT: IC5.7 (~SHDN), IC6.7 (~SHDN), IC8.7 (~SHDN), IC9.7 (~SHDN), IC11.7 (~SHDN)
SPI1_MOSI: IC5.8 (SDI), IC6.8 (SDI), IC8.8 (SDI), IC9.8 (SDI), IC10.17 (PA7), IC11.8 (SDI), J3.9
SPI1_SCK: IC5.9 (CLK), IC6.9 (CLK), IC8.9 (CLK), IC9.9 (CLK), IC10.15 (PA5), IC11.9 (CLK), J3.10
SPI2_MOSI: IC1.1 (DIN), IC10.28 (PB15), J3.11
SPI2_SCK: IC1.13 (CLK), IC10.21 (PB10), J3.12
SWCLK: IC10.37 (PA14), J19.3
SWDIO: IC10.34 (PA13), J19.2
Vmp: U1.1, U1.2 (-), U1.5 (+), U1.10 (+), U1.12 (+), U9.5 (+), U9.10 (+)
cs_leds: IC1.12 (LOAD_(~CS)), IC2.12 (LOAD_(~CS)), IC10.20 (PB2), J3.3
laag1_1: U4.2 (Y_0), U17.14 (Y_00)
laag1_2: U4.3 (Y_1), U17.15 (Y_01)
laag1_3: U4.4 (Y_2), U17.16 (Y_02)
laag1_4: U4.5 (Y_3), U17.17 (Y_03)
laag1_5: U4.6 (Y_4), U17.18 (Y_04)
laag1_6: U4.7 (Y_5), U17.19 (Y_05)
laag1_7: U4.8 (Y_6), U17.20 (Y_06)
laag1_8: U4.9 (Y_7), U17.21 (Y_07)
laag1_9: U4.10 (Y_8), U17.22 (Y_08)
laag1_10: U4.11 (Y_9), U17.23 (Y_09)
laag1_11: U4.12 (Y_10), U17.24 (Y_010)
laag1_12: U4.13 (Y_11), U17.25 (Y_011)
laag2_1: U2.2 (Y_0), U16.14 (Y_00)
laag2_2: U2.3 (Y_1), U16.15 (Y_01)
laag2_3: U2.4 (Y_2), U16.16 (Y_02)
laag2_4: U2.5 (Y_3), U16.17 (Y_03)
laag2_5: U2.6 (Y_4), U16.18 (Y_04)
laag2_6: U2.7 (Y_5), U16.19 (Y_05)
laag2_7: U2.8 (Y_6), U16.20 (Y_06)
laag2_8: U2.9 (Y_7), U16.21 (Y_07)
laag2_9: U2.10 (Y_8), U16.22 (Y_08)
laag2_10: U2.11 (Y_9), U16.23 (Y_09)
laag2_11: U2.12 (Y_10), U16.24 (Y_010)
laag2_12: U2.13 (Y_11), U16.25 (Y_011)
laag3_1: U3.2 (Y_0), U14.14 (Y_00)
laag3_2: U3.3 (Y_1), U14.15 (Y_01)
laag3_3: U3.4 (Y_2), U14.16 (Y_02)
laag3_4: U3.5 (Y_3), U14.17 (Y_03)
laag3_5: U3.6 (Y_4), U14.18 (Y_04)
laag3_6: U3.7 (Y_5), U14.19 (Y_05)
laag3_7: U3.8 (Y_6), U14.20 (Y_06)
laag3_8: U3.9 (Y_7), U14.21 (Y_07)
laag3_9: U3.10 (Y_8), U14.22 (Y_08)
laag3_10: U3.11 (Y_9), U14.23 (Y_09)
laag3_11: U3.12 (Y_10), U14.24 (Y_010)
laag3_12: U3.13 (Y_11), U14.25 (Y_011)
laag_1: IC3.33 (TX0), J18.12, U6.2 (Y_0), U13.2 (Y_0)
laag_2: IC3.32 (TX1), J18.11, U6.3 (Y_1), U13.3 (Y_1)
laag_3: IC3.31 (TX2), J18.10, U6.4 (Y_2), U13.4 (Y_2)
laag_4: IC3.30 (TX3), J18.9, U6.5 (Y_3), U13.5 (Y_3)
laag_5: IC3.34 (TX4), J18.8, U6.6 (Y_4), U13.6 (Y_4); also elsewhere on the board
laag_6: IC3.38 (TX5), J18.7, U6.7 (Y_5), U13.7 (Y_5); also elsewhere on the board
laag_7: IC3.37 (TX6), J18.6, U6.8 (Y_6), U13.8 (Y_6)
laag_8: IC3.36 (TX7), J18.5, U6.9 (Y_7), U13.9 (Y_7)
laag_9: IC3.35 (TX8), J18.4, U6.10 (Y_8), U13.10 (Y_8); also elsewhere on the board
laag_10: IC3.41 (TX9), J18.3, U6.11 (Y_9), U13.11 (Y_9); also elsewhere on the board
laag_11: IC3.42 (TX10), J18.2, U6.12 (Y_10), U13.12 (Y_10); also elsewhere on the board
laag_12: IC3.43 (TX11), J18.1, U6.13 (Y_11), U13.13 (Y_11)
slider_1: IC3.27 (RX0), J2.1, U6.1 (X_output); also elsewhere on the board
slider_2: IC3.26 (RX1), J8.1, U8.1 (X_output); also elsewhere on the board
slider_3: IC3.25 (RX2), J10.1, U4.1 (X_output); also elsewhere on the board
slider_4: IC3.24 (RX3), J9.1, U2.1 (X_output); also elsewhere on the board
slider_5: IC3.23 (RX4), J11.1, U3.1 (X_output); also elsewhere on the board
slider_6: IC3.22 (RX5), J13.1, U11.1 (X_output); also elsewhere on the board
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
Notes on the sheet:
BASS LIN1
BASS LIN2
MEDIUM LIN2
TREBLE LIN2
MEDIUM LIN1
TREBLE LIN1
LIN1 IN
Line 2 IN
MASTER OUT
MICROFOON VOLUME
L-R
rood
oranje
groen
Component alleen nog bestellen
